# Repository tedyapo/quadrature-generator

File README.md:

# quadrature-generator
Adapter for using spectrum analyzer tracking generator (in zero span) as a digital clock source with I/Q outputs

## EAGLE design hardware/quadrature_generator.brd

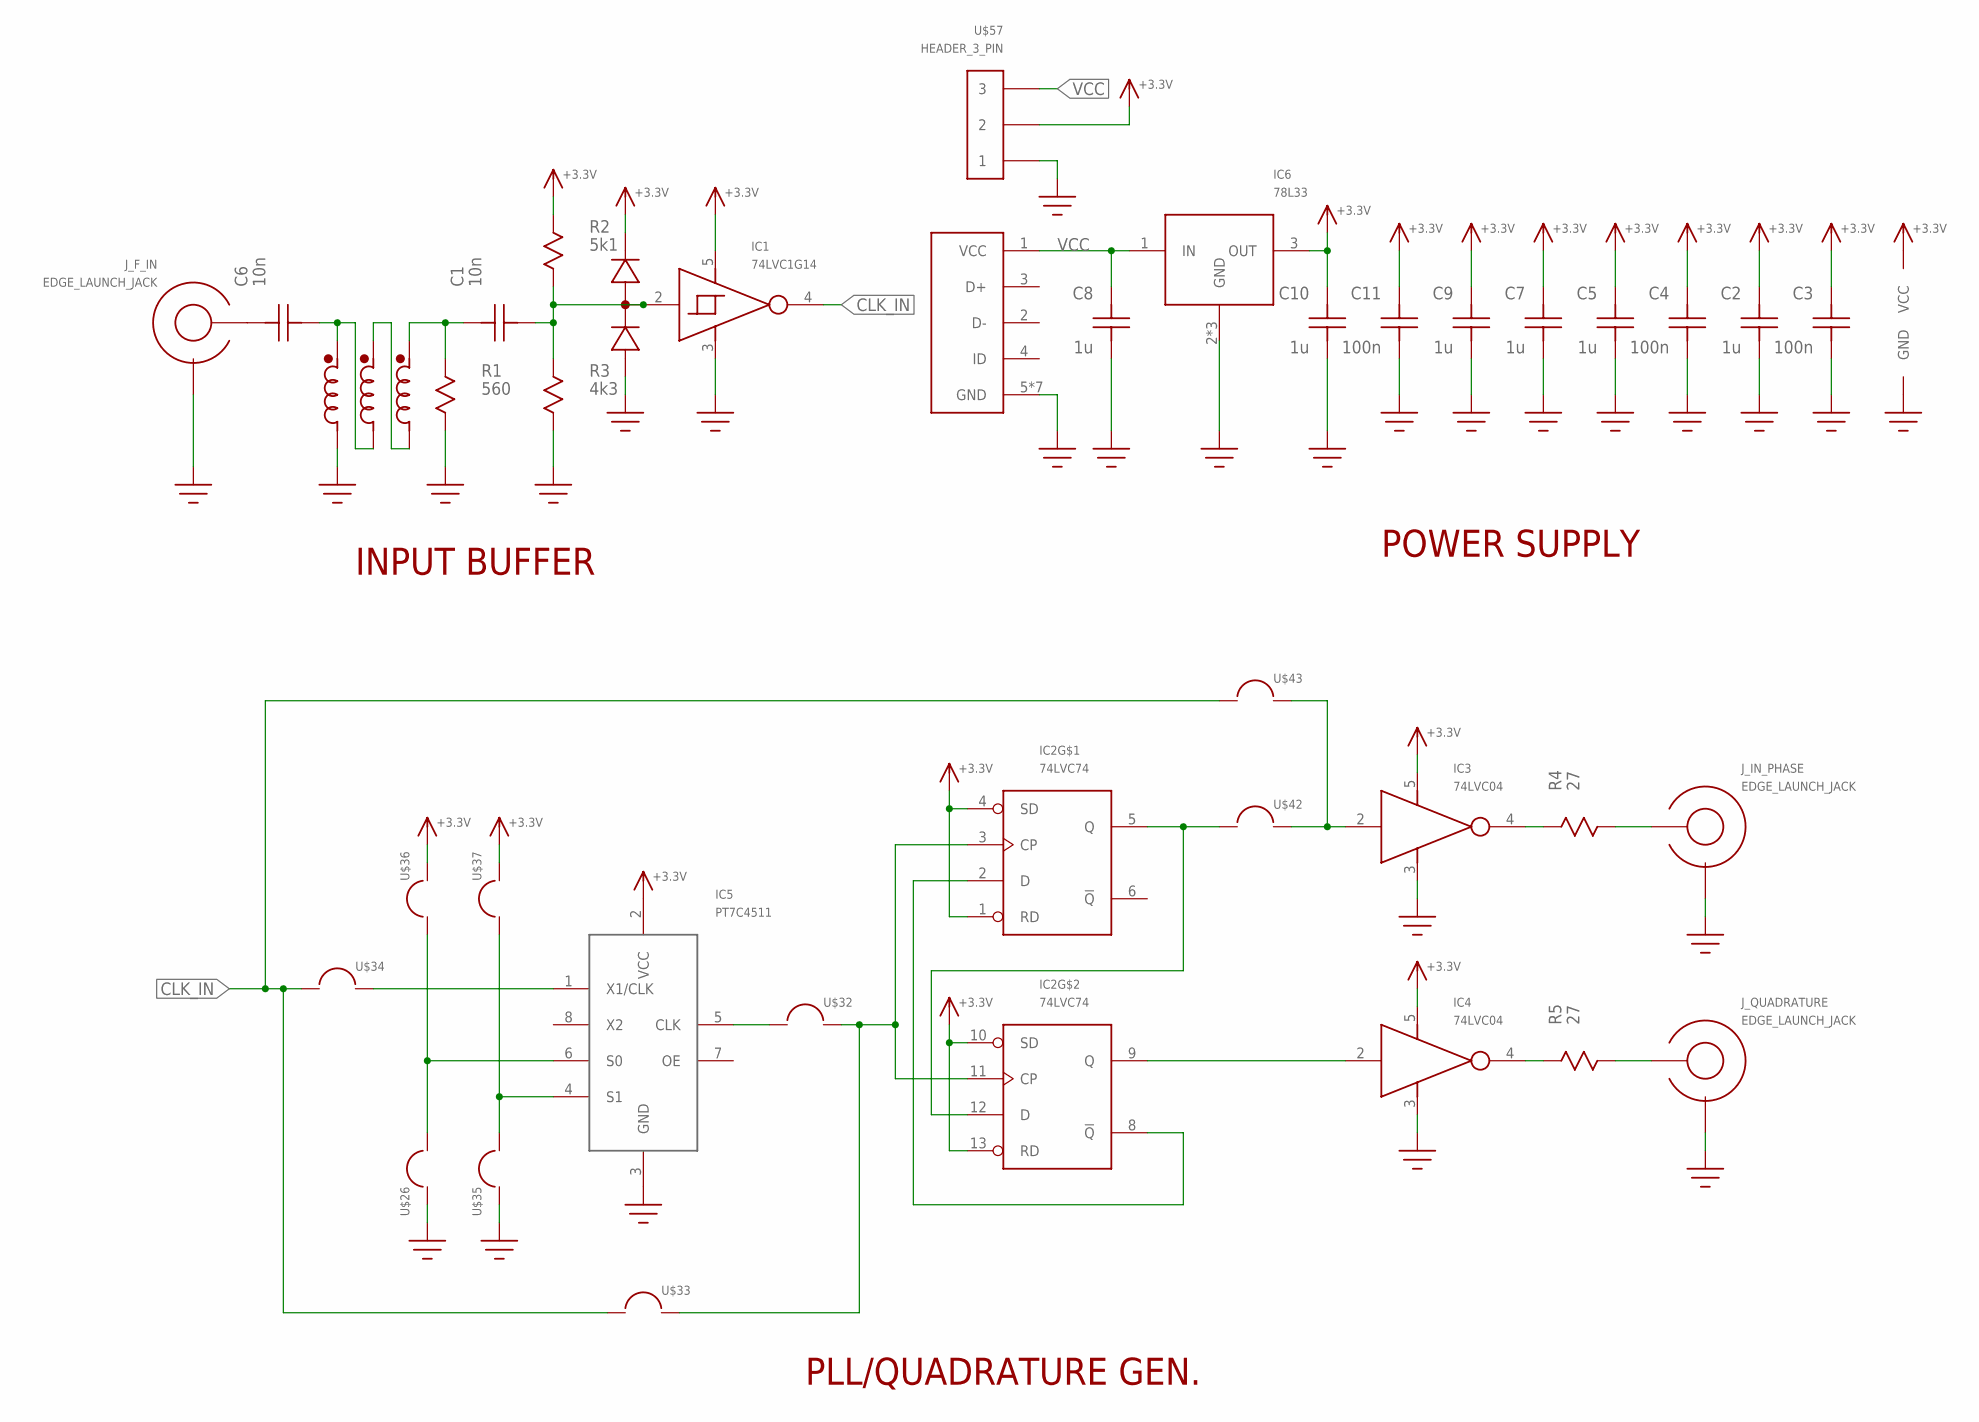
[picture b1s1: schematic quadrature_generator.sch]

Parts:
C1, C6: 10n; 0805
C2, C5, C7, C8, C9, C10: 1u; 0805
C3, C4, C11: 100n; 0805
IC1: 74LVC1G14; SOT23-5
IC2: 74LVC74; SOIC14_NARROW
IC3, IC4: 74LVC04; SOT23-5
IC5: PT7C4511; SOIC8
IC6: 78L33; SOT-89
J_F_IN: EDGE_LAUNCH_JACK; EDGE_LAUNCH_RF_CON
J_IN_PHASE: EDGE_LAUNCH_JACK; EDGE_LAUNCH_RF_CON
J_QUADRATURE: EDGE_LAUNCH_JACK; EDGE_LAUNCH_RF_CON
R1: 560; R1206
R2: 5k1; R0805
R3: 4k3; R0805
R4, R5: 27; R1206
U$1: FT37_TRIFILAR_1; FT37_TRIFILAR_VERT_NC
U$18: USB_JACK; FCI_MICRO_USB
U$26, U$32, U$33, U$34, U$35, U$36, U$37, U$42, U$43: SOLDER_BRIDGE
U$50: MMBD7000L; SOT-23
U$57: HEADER_3_PIN

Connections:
+3.3V: C2.P$1, C3.P$1, C4.P$1, C5.P$1, C7.P$1, C9.P$1, C10.P$1, C11.P$1, IC1.5 (VCC), IC2.1 (RD), IC2.4 (SD), IC2.10 (SD), IC2.13 (RD), IC2.14 (VCC), IC3.5 (VCC), IC4.5 (VCC), IC5.2 (VCC), IC6.3 (OUT), R2.P$1, U$36.2@1, U$36.2@2, U$36.2@3, U$37.2@1, U$37.2@2, U$37.2@3, U$50.2 (CATHODE), U$57.2
CLK_IN: IC1.4 (OUT), U$33.1, U$34.1, U$43.1
GND: C2.P$2, C3.P$2, C4.P$2, C5.P$2, C7.P$2, C8.P$2, C9.P$2, C10.P$2, C11.P$2, IC1.3 (GND), IC2.7 (GND), IC3.3 (GND), IC4.3 (GND), IC5.3 (GND), IC6.2 (GND), IC6.TAB (GND), IC6.TAB@1 (GND), J_F_IN.GND@1 (GND), J_F_IN.GND@2 (GND), J_IN_PHASE.GND@1 (GND), J_IN_PHASE.GND@2 (GND), J_QUADRATURE.GND@1 (GND), J_QUADRATURE.GND@2 (GND), R1.P$2, R3.P$2, U$1.P$R1 (R1), U$18.5 (GND), U$18.GND1 (GND), U$18.GND2 (GND), U$18.GND3 (GND), U$18.GND4 (GND), U$18.GND5 (GND), U$18.GND6 (GND), U$26.2@1, U$26.2@2, U$26.2@3, U$35.2@1, U$35.2@2, U$35.2@3, U$50.1 (ANODE), U$57.1
unnamed: C6.P$1, U$1.P$G1 (G1), U$1.P$R2 (R2)
unnamed: U$1.P$G2 (G2), U$1.P$Y1 (Y1)
unnamed: C1.P$2, R1.P$1, U$1.P$Y2 (Y2)
unnamed: C1.P$1, IC1.2 (IN), R2.P$2, R3.P$1, U$50.3 (COMMON)
unnamed: J_IN_PHASE.SIG, R4.P$2
unnamed: IC3.4 (OUT), R4.P$1
unnamed: IC2.5 (Q), IC2.12 (D), U$42.1
unnamed: IC2.3 (CP), IC2.11 (CP), U$32.2@1, U$32.2@2, U$32.2@3, U$33.2@1, U$33.2@2, U$33.2@3
unnamed: IC2.2 (D), IC2.8 (!Q!)
unnamed: J_QUADRATURE.SIG, R5.P$2
unnamed: IC4.4 (OUT), R5.P$1
unnamed: IC2.9 (Q), IC4.2 (IN)
unnamed: C6.P$2, J_F_IN.SIG
unnamed: IC5.5 (CLK), U$32.1
unnamed: IC5.1 (X1/CLK), U$34.2@1, U$34.2@2, U$34.2@3
unnamed: IC3.2 (IN), U$42.2@1, U$42.2@2, U$42.2@3, U$43.2@1, U$43.2@2, U$43.2@3
S0: IC5.6 (S0), U$26.1, U$36.1
S1: IC5.4 (S1), U$35.1, U$37.1
VCC: C8.P$1, IC6.1 (IN), U$18.1 (VCC), U$57.3

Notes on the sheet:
INPUT BUFFER
POWER SUPPLY
PLL/QUADRATURE GEN.

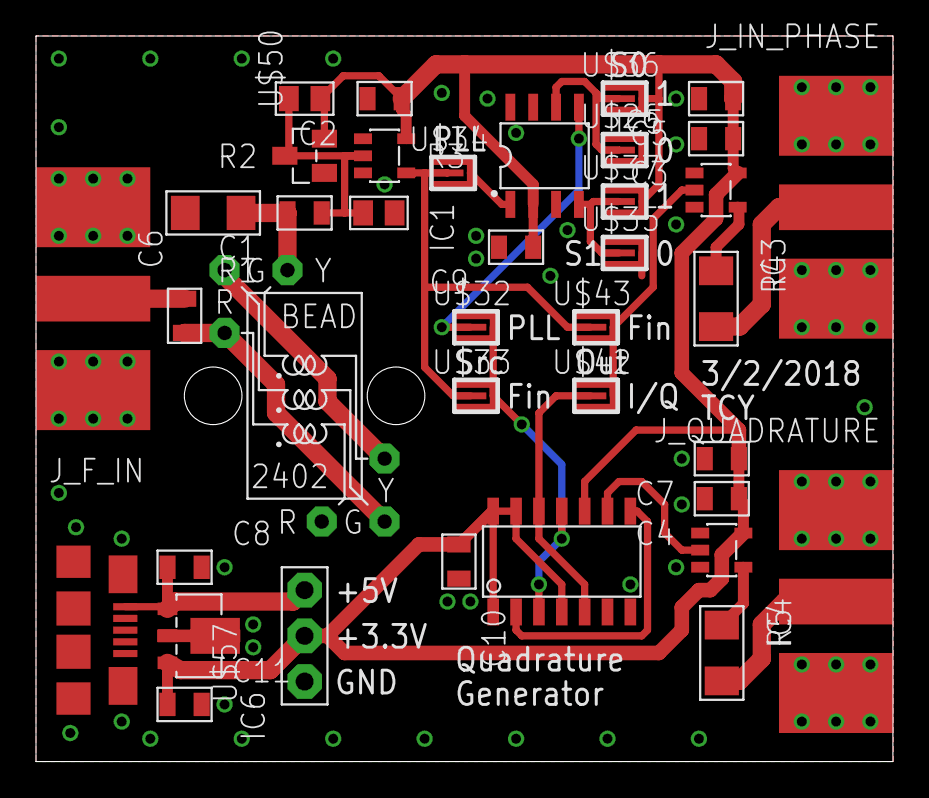
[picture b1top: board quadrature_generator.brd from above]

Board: 2 copper layers, 47.6 x 40.3 mm, 38 parts (0 on the bottom side), 22 nets.

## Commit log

2018-03-02 first checkin
2018-03-02 checkpoint
2018-03-02 first fab
2018-03-02 updated component values
